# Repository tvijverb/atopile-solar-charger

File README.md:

# atopile-solar-charger

## Description
### WARNING: PCB is still untested, it's being produced right now. I'll update the readme after testing.
Solar charger PCB using the Texas Instruments BQ25504. It is meant to be paired with a LIC supercap https://www.aliexpress.com/w/wholesale-lic-supercapacitor.html?spm=a2g0o.home.search.0
Pairing it with a regular 3.7V lithium battery is not recommended since the undervoltage value is too low for this chemistry.

Solar input - 3V max

Battery voltage range

| Specs | Voltage |
| --- | --- |
| Vbat_ov | 3.8 |
| Vbat_uv | 2.5 |
| Vbat_ok | 2.6 |

# Design files
The JLCPCB production files can be found in the following folder
```
elec/layout/default/production
```

## Connectors
There are 3 2-pin JST connectors with a 2mm pitch. Positive and negative pins are indicated with a + sign on the top of the PCB.
1. Solar input
2. battery connector
3. load output

## Silkscreen
The component silkscreen labels have not been modified (yet) from default settings. These will cause warnings in KiCad DRC checks.

## Atopile CI/CD
The atopile CI/CD github action pipeline will currently give errors since I used my own parts-search endpoint. This will probably be fixed in the coming weeks.

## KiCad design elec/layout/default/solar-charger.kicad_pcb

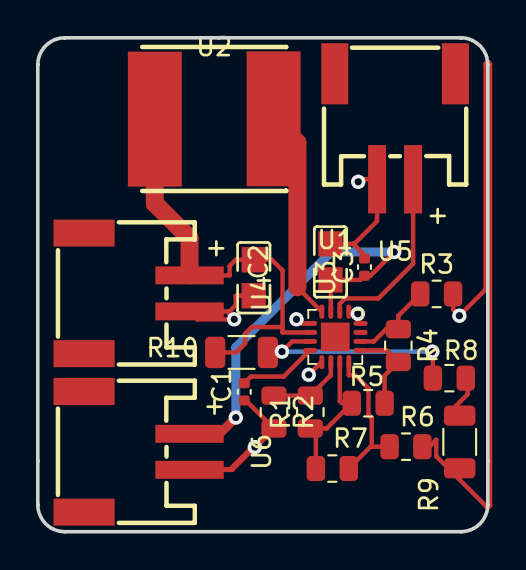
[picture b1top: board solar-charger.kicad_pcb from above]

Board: 2 copper layers, 25.0 x 27.4 mm, 19 parts (0 on the bottom side), 13 nets.

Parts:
C1: 50V 10nF X7R ±10% 0402 Multilayer Ceramic Capacit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; C0402
C2: 25V 4.7uF X5R ±10% 0805 Multilayer Ceramic Capaci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; C0805
C3: 16V 100nF X7R ±10% 0402 Multilayer Ceramic Capaci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; C0402
R1: 125mW Thick Film Resistors 150V ±100ppm/℃ ±1% 5.1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; R0805
R2: 125mW Thick Film Resistors 150V ±100ppm/℃ ±1% 4.8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; R0805
R3: 125mW Thick Film Resistors 150V ±100ppm/℃ ±1% 4.4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; R0805
R4: 125mW Thick Film Resistors 150V ±100ppm/℃ ±1% 4.7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; R0805
R5: 125mW Thick Film Resistors ±100ppm/℃ ±1% 715kΩ 08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; R0805
R6, R7: 125mW Thick Film Resistors ±100ppm/℃ ±1% 4.99MΩ 0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; R0805
R8: 125mW Thick Film Resistors 150V ±100ppm/℃ ±1% 6.0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; R0805
R9: 250mW Thick Film Resistors 200V ±100ppm/℃ ±1% 10M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; R1206
R10: 250mW Thick Film Resistors 200V ±100ppm/℃ ±1% 4.0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; R1206
U1: VQFN-16_L3.0-W3.0-P0.50-TL-EP
U2: IND-SMD_L8.0-W8.0_FNR80XXS
U3: C0805
U4, U5, U6: CONN-SMD_P2.00_S2B-PH-SM4-TB-LF-SN

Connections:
_1: R10.2, U1.2, U2.1, U3.1, U4.1
gnd: C1.2, C2.2, C3.2, R2.2, R3.2, R6.2, R9.2, U1.1, U1.5, U1.12, U1.13, U3.2, U4.2, U5.2, U6.2
lbst: U1.16, U2.2
ok_hyst: R4.2, R5.1, U1.9
ok_prog: R3.1, R4.1, U1.10
p2: R8.2, R9.1
vbat: U1.14, U5.1
vbat_ov: R1.2, R2.1, U1.6
vbat_uv: R6.1, R7.2, U1.8
vcc: C2.1, C3.1, U1.15, U6.1
voc_samp: R8.1, R10.1, U1.3
vrdiv: R1.1, R5.2, R7.1, U1.7
vref_samp: C1.1, U1.4

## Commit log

2024-02-07 Configure project
2024-02-07 solar side done
2024-02-12 design v3
2024-02-13 v1 solar PCB
2024-02-16 will it fix the ci pipeline?
2024-02-19 update component server url
2024-03-20 update components
2024-06-24 solar charger fix gnd connections
2024-06-24 remove batteries dependency
2024-06-24 update backside graphics
